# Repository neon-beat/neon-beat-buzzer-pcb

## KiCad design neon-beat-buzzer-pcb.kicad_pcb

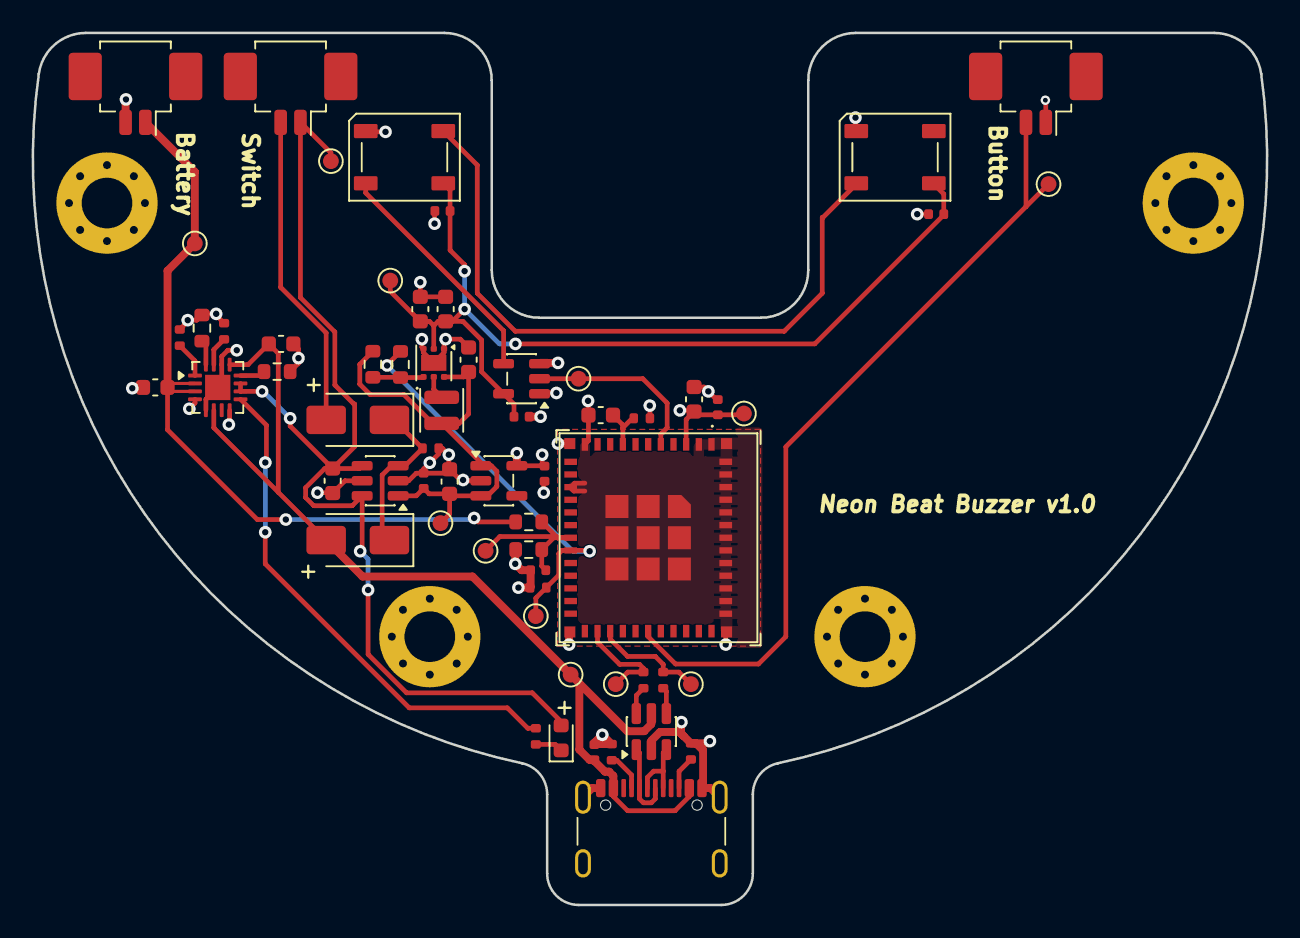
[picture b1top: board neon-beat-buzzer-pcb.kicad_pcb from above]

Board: 4 copper layers, 78.0 x 55.1 mm, 66 parts (0 on the bottom side), 32 nets.

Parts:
C1: 4.7uF; C_0603_1608Metric
C2, C3, C11, C14: 1uF; C_0603_1608Metric
C4, C5, C6, C9: 10uF; C_0603_1608Metric
C7, C10: 100nF; C_0402_1005Metric
C8, C12, C13, C15, C16, C17: 0.1uF; C_0402_1005Metric
D3, D4: WS2812B; LED_WS2812B_PLCC4_5.0x5.0mm_P3.2mm
D5: LED; LED_0603_1608Metric
D7, D8: D_Schottky; D_SMA
H1, H2, H3, H4: MountingHole_3.2mm_M3_Pad_Via
J1: BATT_CON; Molex_PicoBlade_53261-0271_1x02-1MP_P1.25mm_Horizontal
J2: SWITCH_CON; Molex_PicoBlade_53261-0271_1x02-1MP_P1.25mm_Horizontal
J3: BUTTON_CON; Molex_PicoBlade_53261-0271_1x02-1MP_P1.25mm_Horizontal
J4: USB_C_Receptacle_USB2.0_16P; USB_C_Receptacle_GCT_USB4105-xx-A_16P_TopMnt_Horizontal
L1: 2.2uH; L_APV_ANR252010
R1, R2: 5.1k; R_0402_1005Metric
R3, R4: 22; R_0402_1005Metric
R5, R9, R15, R16: 10k; R_0402_1005Metric
R6: 1.8k; R_0603_1608Metric
R7: 3k; R_0603_1608Metric
R8: 1k; R_0402_1005Metric
R10: 68k; R_0603_1608Metric
R11: 220k; R_0603_1608Metric
R12: 1.5k; R_0402_1005Metric
R13, R14: 0; R_0603_1608Metric
TP1, TP2, TP3, TP4, TP5, TP6, TP7, TP8, TP9, TP10, TP11, TP12: TestPoint_Pad_D1.0mm
U1: ESP32-C3-MINI-1; ESP32-C3-MINI-1U
U2: BQ24074RGT; VQFN-16-1EP_3x3mm_P0.5mm_EP1.6x1.6mm
U3: TPS22929D; SOT-23-6
U4: 74AHCT1G125; SOT-23-5
U5: TPS610997DRV; WSON-6-1EP_2x2mm_P0.65mm_EP1x1.6mm
U6: USBLC6-2SC6; SOT-23-6
U7: XC6210B332MR; SOT-23-5

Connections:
/boost_en: R13.1, R16.1, TP12.1 (1_1), U1.19 (GPIO5/ADC2_CH0)
/button: J3.2, TP10.1 (1_1), U1.30 (GPIO20/U0RXD)
/chg: R12.2, U2.9 (~CHG)
/esp_usb_dm: R4.2, TP8.1 (1_1), U1.26 (GPIO18/USB_D-)
/esp_usb_dp: R3.2, TP7.1 (1_1), U1.27 (GPIO19/USB_D+)
/led: TP9.1 (1_1), U1.5 (GPIO2/ADC1_CH2), U4.2
/switch: D7.2 (A), J2.2
/v_3v3: C8.1, C9.1, C13.1, J3.1, R9.2, TP5.1 (1_1), U1.3 (3V3), U7.5 (VOUT)
/v_5v: C5.1, C6.1, C15.1, C16.1, C17.1, D3.1 (VDD), D4.1 (VDD), TP6.1 (1_1), U4.5 (VCC), U5.2 (VOUT)
/v_batt_meas: C7.1, R10.1, R11.2, TP11.1 (1_1), U1.18 (GPIO4/ADC1_CH4)
/v_batt_p: C1.1, J1.1, R11.1, TP1.1 (1_1), U2.2 (BAT), U2.3 (BAT)
/v_ldo: C4.1, C12.1, C14.1, L1.2, R14.2, TP4.1 (1_1), U3.1 (VOUT), U5.6 (VI), U7.1 (VIN), U7.3 (CE)
/v_sys: C11.1, D5.2 (A), J2.1, TP2.1 (1_1), U2.10 (OUT), U2.11 (OUT), U3.4 (VIN), U3.6 (VIN)
/v_usb: C2.1, C10.1, D8.2 (A), J4.A4 (VBUS), J4.A9 (VBUS), J4.B4 (VBUS), J4.B9 (VBUS), TP3.1 (1_1), U2.6 (EN1), U2.13 (IN), U6.5 (VBUS)
GND: C1.2, C2.2, C3.2, C4.2, C5.2, C6.2, C7.2, C8.2, C9.2, C10.2, C11.2, C12.2, C13.2, C14.2, C15.2, C16.2, C17.2, D3.3 (VSS), D4.3 (VSS), H1.1 (1_1), H2.1 (1_1), H3.1 (1_1), H4.1 (1_1), J1.2, J4.A1 (GND), J4.A12 (GND), J4.B1 (GND), J4.B12 (GND), J4.SH (SHIELD), R1.2, R2.2, R5.1, R6.1, R7.2, R8.2, R10.2, R15.2, R16.2, U1.1 (GND), U1.2 (GND), U1.11 (GND), U1.14 (GND), U1.36 (GND), U1.37 (GND), U1.38 (GND), U1.39 (GND), U1.40 (GND), U1.41 (GND), U1.42 (GND), U1.43 (GND), U1.44 (GND), U1.45 (GND), U1.46 (GND), U1.47 (GND), U1.48 (GND), U1.49 (GND), U1.50 (GND), U1.51 (GND), U1.52 (GND), U1.53 (GND), U2.4 (~CE), U2.5 (EN2), U2.8 (VSS), U2.14 (TMR), U2.17 (VSS), U3.2 (GND), U3.5 (GND), U4.1, U4.3 (GND), U5.1 (GND), U5.3 (FB), U5.7 (GND), U6.2 (GND), U7.2 (GND)
unnamed: D3.4 (DIN), U4.4
unnamed: D3.2 (DOUT), D4.4 (DIN)
unnamed: D5.1 (K), R12.1
unnamed: D7.1 (K), D8.1 (K), R15.1, U3.3 (ON)
unnamed: J4.A5 (CC1), R1.1
unnamed: J4.B5 (CC2), R2.1
unnamed: J4.A6 (D+), J4.B6 (D+), U6.3 (I/O2)
unnamed: J4.A7 (D-), J4.B7 (D-), U6.1 (I/O1)
unnamed: R3.1, U6.4 (I/O2)
unnamed: R4.1, U6.6 (I/O1)
unnamed: C3.1, R9.1, U1.8 (EN/CHIP_PU)
unnamed: R7.1, U2.12 (ILIM)
unnamed: R6.2, U2.16 (ISET)
unnamed: R8.1, U2.15 (ITERM)
unnamed: R5.2, U2.1 (TS)
unnamed: R13.2, R14.1, U5.4 (EN)
unnamed: L1.1, U5.5 (SW)

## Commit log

2026-03-21 Initial import
2026-03-21 project: add project local configuration after having disabled backups
2026-03-22 Add main features for the PCB Still missing: - battery measure - charging LED
2026-03-23 schematic: all main features are now on-board
2026-03-23 schematic: fix a handful of issues
    - invert usb signals
    - set power supply on power input pins
    - adjust battery measure divider to fit 1.1v ADC full scale
    - add decoupling capacitors on MCU
2026-03-25 schematic: add esd protection, and add all footprints
2026-03-26 pcb: move all composents in proper place
2026-03-30 schematic: fix multiple points
    - use a LDO with lower drop
    - feed the boost directly with v_sys
    - add a few caps around WS2812 leds
    - fix mistake on the boost enable pin
2026-03-30 pcb: add layout from Freecad
2026-03-30 git: add basic .gitignore
2026-03-30 project: partial routing
2026-04-05 3d: add missing 3d views
    Add 3d models for molex connector and battery charger
2026-04-05 pcb: add updated edge cut
2026-04-05 gitignore: ignore board step file
2026-04-05 project: add routed board
    - Board is now fully routed (and needs some review)
    - Tooling holes are added
    - Needs to complete BOM
2026-05-03 pcb: a few adjustments
    Mostly setting a few power sources on the schematic
2026-05-10 board: fix layout
    Move the boost input from v_sys to v_ldo. Update the PCB accordingly.
    While at it, import JLCPCB design rules. There are still a lot of
    silkscreen clearance issues to fix.
2026-05-10 pcb: fix all DRC errors
    Many components had some silkscreen clearance issue regarding JLCPCB
    constraints. Fixed those by:
    - editing the library footprint
    - duplicating the footprint into a user library
    - removing the faulty silkscreen
    - updating all components using this footprint with the override one
